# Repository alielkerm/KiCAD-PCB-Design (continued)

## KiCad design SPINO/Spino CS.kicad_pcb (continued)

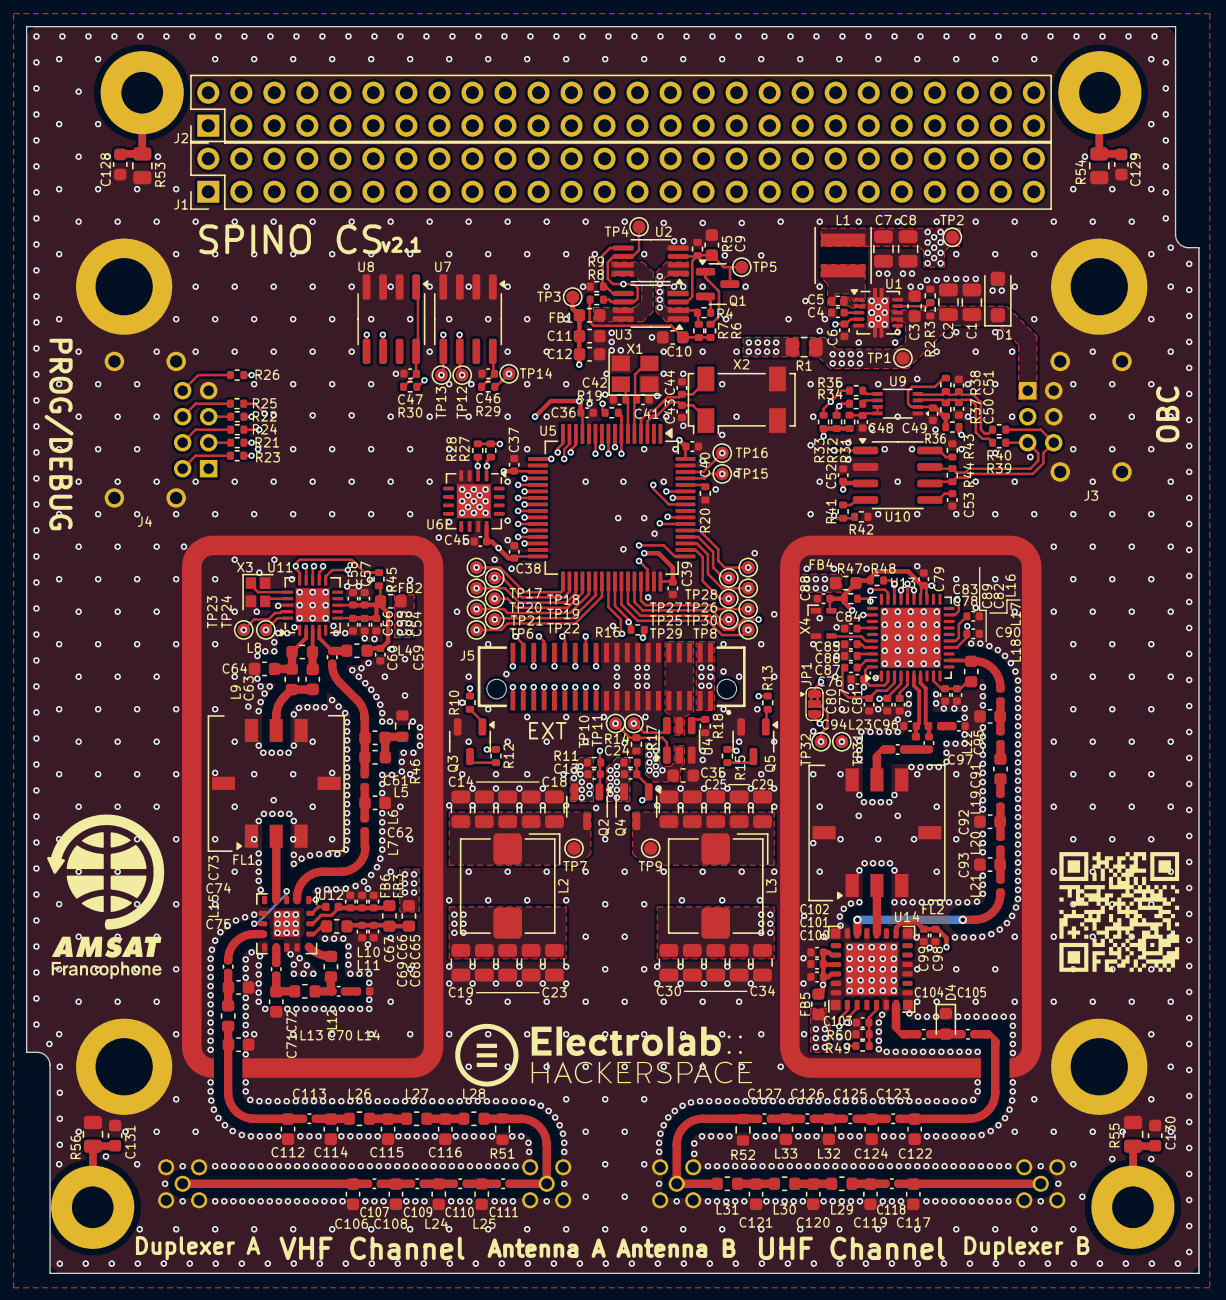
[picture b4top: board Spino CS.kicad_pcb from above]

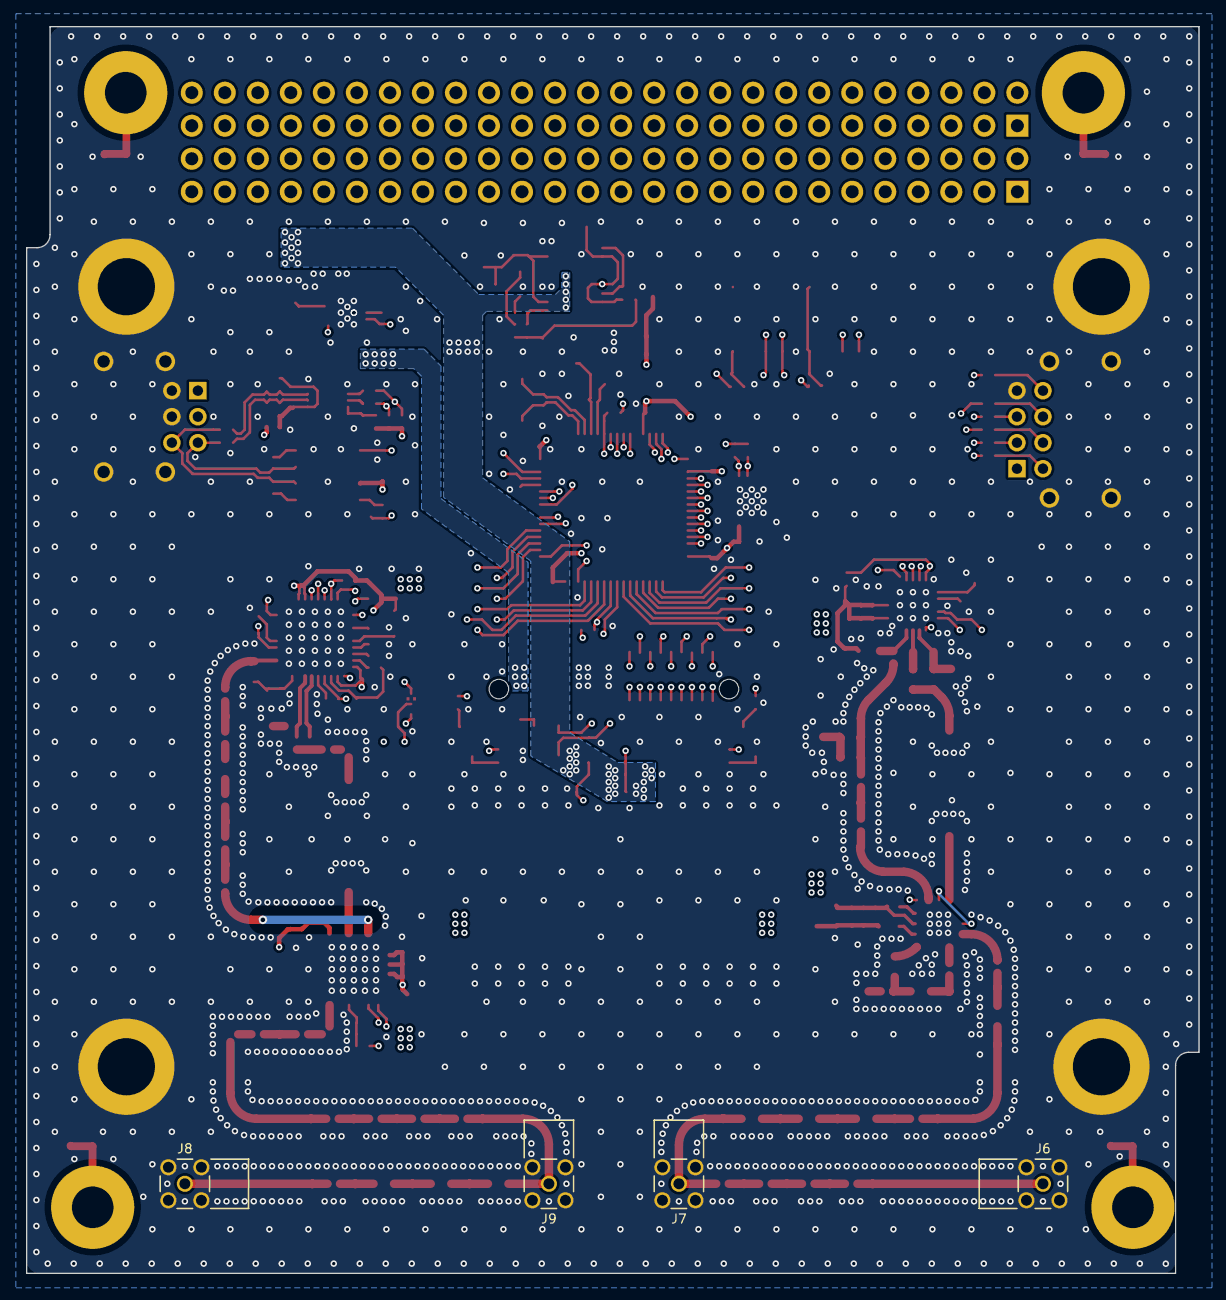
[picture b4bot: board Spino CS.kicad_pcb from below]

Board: 4 copper layers, 90.2 x 95.9 mm, 305 parts (4 on the bottom side), 175 nets.

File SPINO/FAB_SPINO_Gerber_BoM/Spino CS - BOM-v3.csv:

Comment,Designator,Footprint
4.7u,"C1,C2",GCM21BC7YA475KE36L 
100n,C3,GCM188R71H104JA57D
1u,"C4,C54,C57,C65,C68,C98,C100,C103",GCM155C71A105KE38D
100n,"C5,C13,C24,C36,C37,C38,C39,C40,C45,C46,C47,C48,C49,C55,C58,C76,C77,C78,C79,C88",GCM155R71C104KA55D
10n,C6,GCM155R71E103KA37D
10u,"C7,C8,C14,C15,C16,C17,C18,C19,C20,C21,C22,C23,C25,C26,C27,C28,C29,C30,C31,C32,C33,C34",GCM21BR71A106KE22K
1u,"C9,C10,C35",GCM188R71C105KA64D
2.2u,"C11,C12",GCM188R70J225KE22D
18p,"C41,C42",GCM1555C1H180FA16D
6.2p,"C43,C44",GCM1555C1H6R2BA16D
100p,"C56,C73,C113,C123",GCM1555C1H101FA16D
220n,"C59,C80,C81,C82,C83,C84,C85,C86",GCM155R71C224KE02D
470p,C60,GCM1555C1H471FA16D
12p,"C61,C64,C74,C75",GCM1885C2A120FA16D
18p,C62,GCM1885C2A180FA16D
6.2p,C63,GCM1885C2A6R2BA16D
1.2n,"C66,C67,C87,C101",GCM155R72A122KA37D
4.7n,C69,GCM155R71H472KA37D
82p,"C70,C89",GCM1555C1H820FA16D
27p,C71,GCM1885C2A270FA16D
2.2n,"C72,C104,C105",GCM155R71H222KA37D
6.8p,"C90,C92,C93",GCM1885C2A6R8BA16D
270p,C91,GCM1885C2A271FA16D
2.7p,C94,GCM1555C1H2R7WA16D
4.8p,"C95,C126",GCQ1555C1H4R2BB01D
270p,"C96,C97",GCM1555C1H271FA16D 
220p,"C99,C102",GCM1555C1H221FA16D
22p,"C115,C116",GCM1885C2A220FA16D
8.4p,"C125,C127",GCQ1555C1H8R4BB01D
3.3V/36V,D1,SMF3.3/SMF4L33A
30V,D4,EZAEG3A50AV
600@100M,"FB1,FB2,FB3,FB4,FB5,FB6",742792651
RBP-140+,FL1,RBP-140+
RBP-440+,FL2,RBP-440+
EXT,J5,LSEM-120-03.0-L-DV-A-N-K-TR
4.7u,L1,XAL4030-472MEC
15u,"L2,L3",CLF7045NIT-150M-D
390n,L4,0603DC-R39XJRW
82n,"L5,L16",0603DC-82NXJRW
47n,L6,0402DC-47NXGRW
68n,L7,0402DC-68NXGRW
220n,L8,0603DC-R22XJRW
150n,L9,0603DC-R15XJRW
15n,L10,0402DC-15NXJRW
10n,L11,0603DC-10NXJRW
7.5n,L12,0603DC-7N5XGRW
27n,L13,0603DC-27NXGRW
2.2n,L14,0402DC-2N2XJRW
44n,"L15,L26,L28",LQW18AN44NG80D
23n,L17,0402DC-23NXGRW
19n,"L18,L19,L21,L22",0402HP-19NXGRW
33n,L20,0402DC-33NXGRW
13n,L23,0402HP-13NXGRW
78n,L27,LQW18AN78NG80D
18n,"L32,L33",0603DC-18NXGRW
BC807,Q1,BC807-40-7-F
BSS215P,"Q2,Q4",BSS215PH6327XTSA1
BC817,"Q3,Q5", BC817-16-7-F 
0,"R3,R49",CRCW04020000Z0ED
22k,"R4,R6",CRCW040222K0FKED
100k,"R5,R7,R10,R11,R13,R14,R16,R17,R19,R20,R31,R32,R33,R45,R47,R48",CRCW0402100KFKED
10k,"R8,R27,R28",CRCW040210K0FKED
"24,9k",R9,CRCW040224K9FKED
47k,"R12,R15",CRCW040247K0FKED
1.15k,R18,CRCW04021K15FKED 
22,"R21,R22,R23,R24,R25,R26,R29,R30,R39,R40",CRCW040222R0FKED
220,"R34,R35,R36",CRCW0402220RFKED
49.9,R46,CRCW060349R9FKEA
10k,"R51,R52",CRCW060310K0FKEA
LM536013-Q1,U1,LM536013QDSXRQ1
MAX892L,"U2,U3",MAX892LEUA+T
TPS22950,U4,TPS22950CQDDCRQ1
STM32L451,U5,STM32L451RET6
ADT7420,U6,ADT7420UCPZ-RL7
FM24C64B,"U7,U8",FM24C16B-GTR
PCA9306DC1,U9,PCA9306TDCURQ1
Si4463,U11,SI4463-C2A-GMR
SKY65367,U12,SKY65367-11
ADF7030,U13,ADF7030-1BCPZN
SKY65377,U14,SKY65377-21
8M,X1, ABM8AIG-8.000MHZ-1Z-T 
32.768k,X2,ABS25-32.768KHZ-6-T
30M,X3,8.30E+11
26M,X4,7Z-26.000MBG-T

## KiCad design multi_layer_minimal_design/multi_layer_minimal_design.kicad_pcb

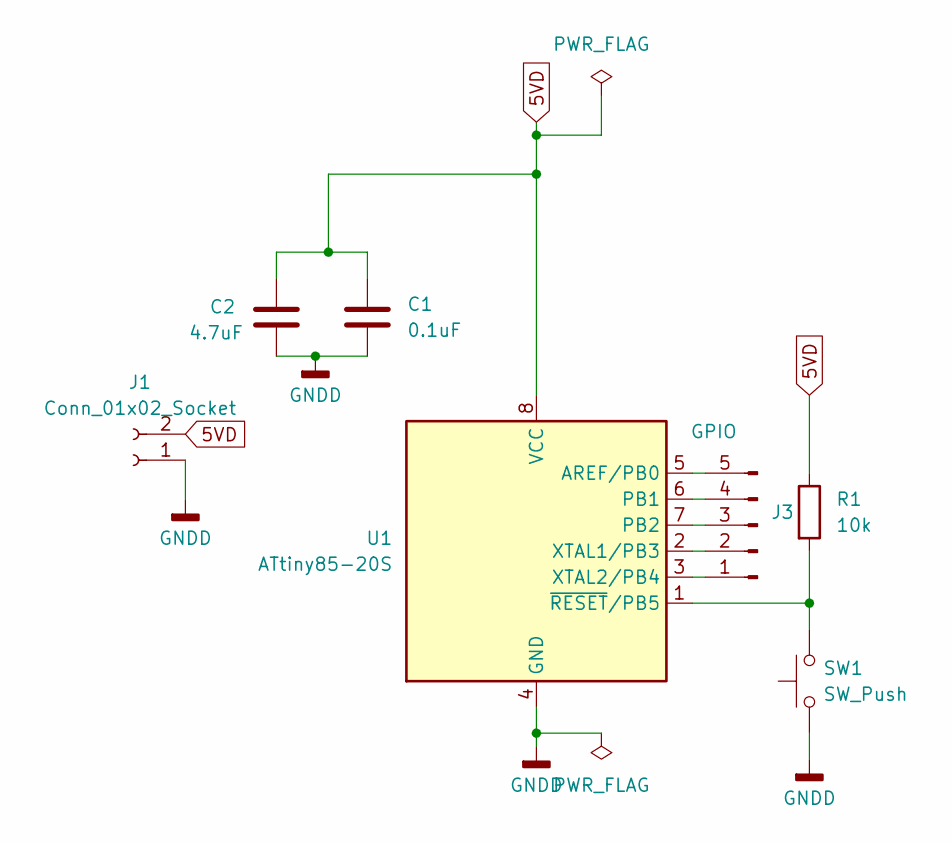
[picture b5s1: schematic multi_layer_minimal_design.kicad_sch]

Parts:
C1: 0.1uF; C_0603_1608Metric
C2: 4.7uF; C_0603_1608Metric
J1: Conn_01x02_Socket; PinHeader_1x02_P2.54mm_Vertical
J3: GPIO; PinHeader_1x05_P2.54mm_Vertical
R1: 10k; R_0603_1608Metric
SW1: SW_Push; SW_PUSH_6mm
U1: ATtiny85-20S; SOIC-8_3.9x4.9mm_P1.27mm

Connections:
5VD: C1.1, C2.1, J1.2, R1.1, U1.8 (VCC)
GNDD: C1.2, C2.2, J1.1, SW1.1, U1.4 (GND)
unnamed: J3.1, U1.3 (XTAL2/PB4)
unnamed: J3.2, U1.2 (XTAL1/PB3)
unnamed: J3.3, U1.7 (PB2)
unnamed: J3.4, U1.6 (PB1)
unnamed: J3.5, U1.5 (AREF/PB0)
unnamed: R1.2, SW1.2, U1.1 (~RESET/PB5)

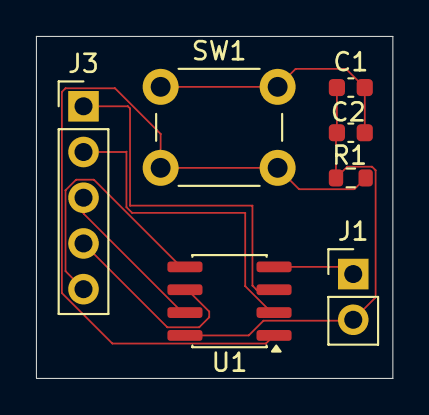
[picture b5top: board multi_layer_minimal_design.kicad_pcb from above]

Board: 4 copper layers, 19.8 x 19.0 mm, 7 parts (0 on the bottom side), 8 nets.

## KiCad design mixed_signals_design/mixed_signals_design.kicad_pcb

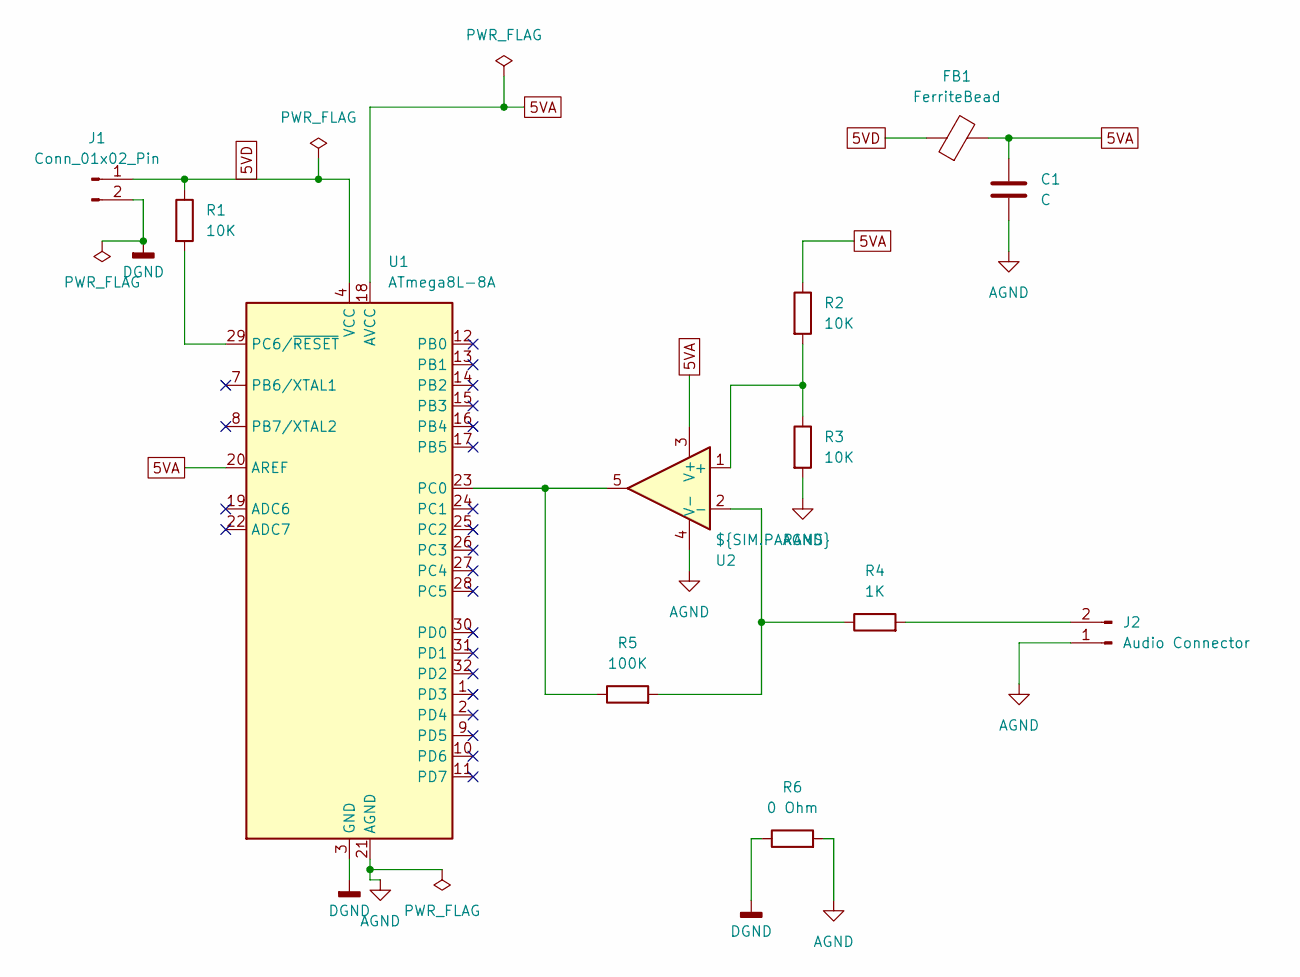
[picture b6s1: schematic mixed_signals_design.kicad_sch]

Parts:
C1: C; C_0603_1608Metric
FB1: FerriteBead; L_0603_1608Metric
J1: Conn_01x02_Pin; PinHeader_1x02_P2.54mm_Vertical
J2: Audio Connector; PinHeader_1x02_P2.54mm_Vertical
R1, R2, R3: 10K; R_0603_1608Metric
R4: 1K; R_0603_1608Metric
R5: 100K; R_0603_1608Metric
R6: 0 Ohm; R_0603_1608Metric
U1: ATmega8L-8A; TQFP-32_7x7mm_P0.8mm
U2: ${SIM.PARAMS}; SOIC-8_3.9x4.9mm_P1.27mm

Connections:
5VA: C1.1, FB1.2, R2.1, U1.18 (AVCC), U1.20 (AREF), U2.3 (V+)
5VD: FB1.1, J1.1, R1.1, U1.4 (VCC), U1.6 (VCC)
AGND: C1.2, J2.1, R3.2, R6.2, U1.21 (AGND), U2.4 (V-)
DGND: J1.2, R6.1, U1.3 (GND), U1.5 (GND)
unnamed: J2.2, R4.2
unnamed: R5.1, U1.23 (PC0), U2.5
unnamed: R1.2, U1.29 (PC6/~RESET)
unnamed: R2.2, R3.1, U2.1 (+)
unnamed: R4.1, R5.2, U2.2 (-)

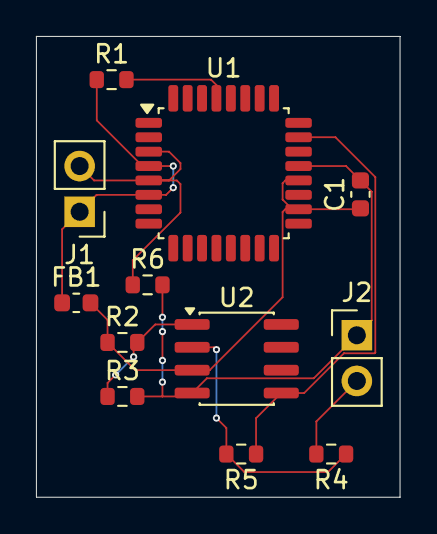
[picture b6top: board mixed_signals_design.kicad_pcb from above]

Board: 2 copper layers, 20.2 x 25.6 mm, 12 parts (0 on the bottom side), 9 nets.

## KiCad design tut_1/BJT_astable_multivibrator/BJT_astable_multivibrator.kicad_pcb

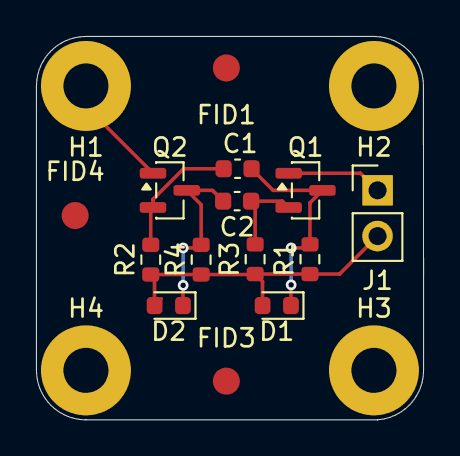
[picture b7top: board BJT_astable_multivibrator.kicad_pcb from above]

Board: 2 copper layers, 21.5 x 21.3 mm, 18 parts (0 on the bottom side), 6 nets.

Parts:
C1, C2: 220uF; C_0603_1608Metric
D1, D2: LED; LED_0603_1608Metric
FID1, FID3, FID4: Fiducial; Fiducial_1.5mm_Mask3mm
H1, H2, H3, H4: MountingHole_Pad; MountingHole_2.5mm_Pad
J1: POWER INPUT; PinHeader_1x02_P2.54mm_Vertical
Q1, Q2: 2N3904; SOT-23
R1, R4: 1K; R_0603_1608Metric
R2, R3: 5K; R_0603_1608Metric

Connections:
GND: H1.1, H2.1, H3.1, H4.1, J1.1, Q1.1 (E), Q2.1 (E)
unnamed: C1.1, D1.1 (K), Q1.3 (C), R1.2
unnamed: C2.2, D2.1 (K), Q2.3 (C), R4.2
VCC: D1.2 (A), D2.2 (A), J1.2, R1.1, R2.1, R3.1, R4.1
bjt_1: C2.1, Q1.2 (B), R3.2
bjt_2: C1.2, Q2.2 (B), R2.2

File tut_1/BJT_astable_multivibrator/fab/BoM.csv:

"Reference","Qty","Value","DNP","Exclude from BOM","Exclude from Board","Footprint","Datasheet"
"C1,C2","2","220uF","","","","Capacitor_SMD:C_0603_1608Metric","~"
"D1,D2","2","LED","","","","LED_SMD:LED_0603_1608Metric","~"
"FID1,FID2,FID3,FID4","4","Fiducial","","Excluded from BOM","","Fiducial:Fiducial_1.5mm_Mask3mm","~"
"H1,H2,H3,H4","4","MountingHole_Pad","","Excluded from BOM","","MountingHole:MountingHole_2.5mm_Pad","~"
"J1","1","POWER INPUT","","","","Connector_PinHeader_2.54mm:PinHeader_1x02_P2.54mm_Vertical","~"
"Q1,Q2","2","2N3904","","","","Package_TO_SOT_SMD:SOT-23","https://www.onsemi.com/pub/Collateral/2N3903-D.PDF"
"R1,R4","2","1K","","","","Resistor_SMD:R_0603_1608Metric","~"
"R2,R3","2","5K","","","","Resistor_SMD:R_0603_1608Metric","~"

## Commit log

2026-01-06 Initial Commit: Add project files
2026-01-07 Fix typo in README title
2026-01-07 Update project description to specify KiCAD
2026-01-07 Create README.txt for SPINO board
    Added introductory information about SPINO project.
